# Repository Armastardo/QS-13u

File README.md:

# QS-13u

Un teclado 40% de 13u, diseñado por Quark.Works, inspirado en el layout del Bacca40.

## Layouts

[KLE Link](http://www.keyboard-layout-editor.com/#/gists/edd9330d8816866bf59f697946c975f9)

## Case

QS-13G (gummy worm)

Pendiente, buscar tamaño de oring adecuado

| Qty | Item						| Notes							|
|----:|-------------------------------------------------|-------------------------------------------------------|
|   2	| Tornillo M2.5 x 4 mm						| https://www.mcmaster.com/91290A099/		|
|   4	| Tornillo M2.5 x 10 mm					| https://www.mcmaster.com/91290A103/		|
|   1	| XYZ Daughterboard			| https://github.com/xyzz/xyztkl-r2/tree/main/dboard	|

La version heatset ademas utiliza:
https://www.aliexpress.com/item/1005003174906572.html

| Qty | Item						|
|----:|-------------------------------------------------|
|   2	| Insert M2.5 x 3 x 3.5						|
|   4	| Insert M2.5 x 5 x 3.5					|

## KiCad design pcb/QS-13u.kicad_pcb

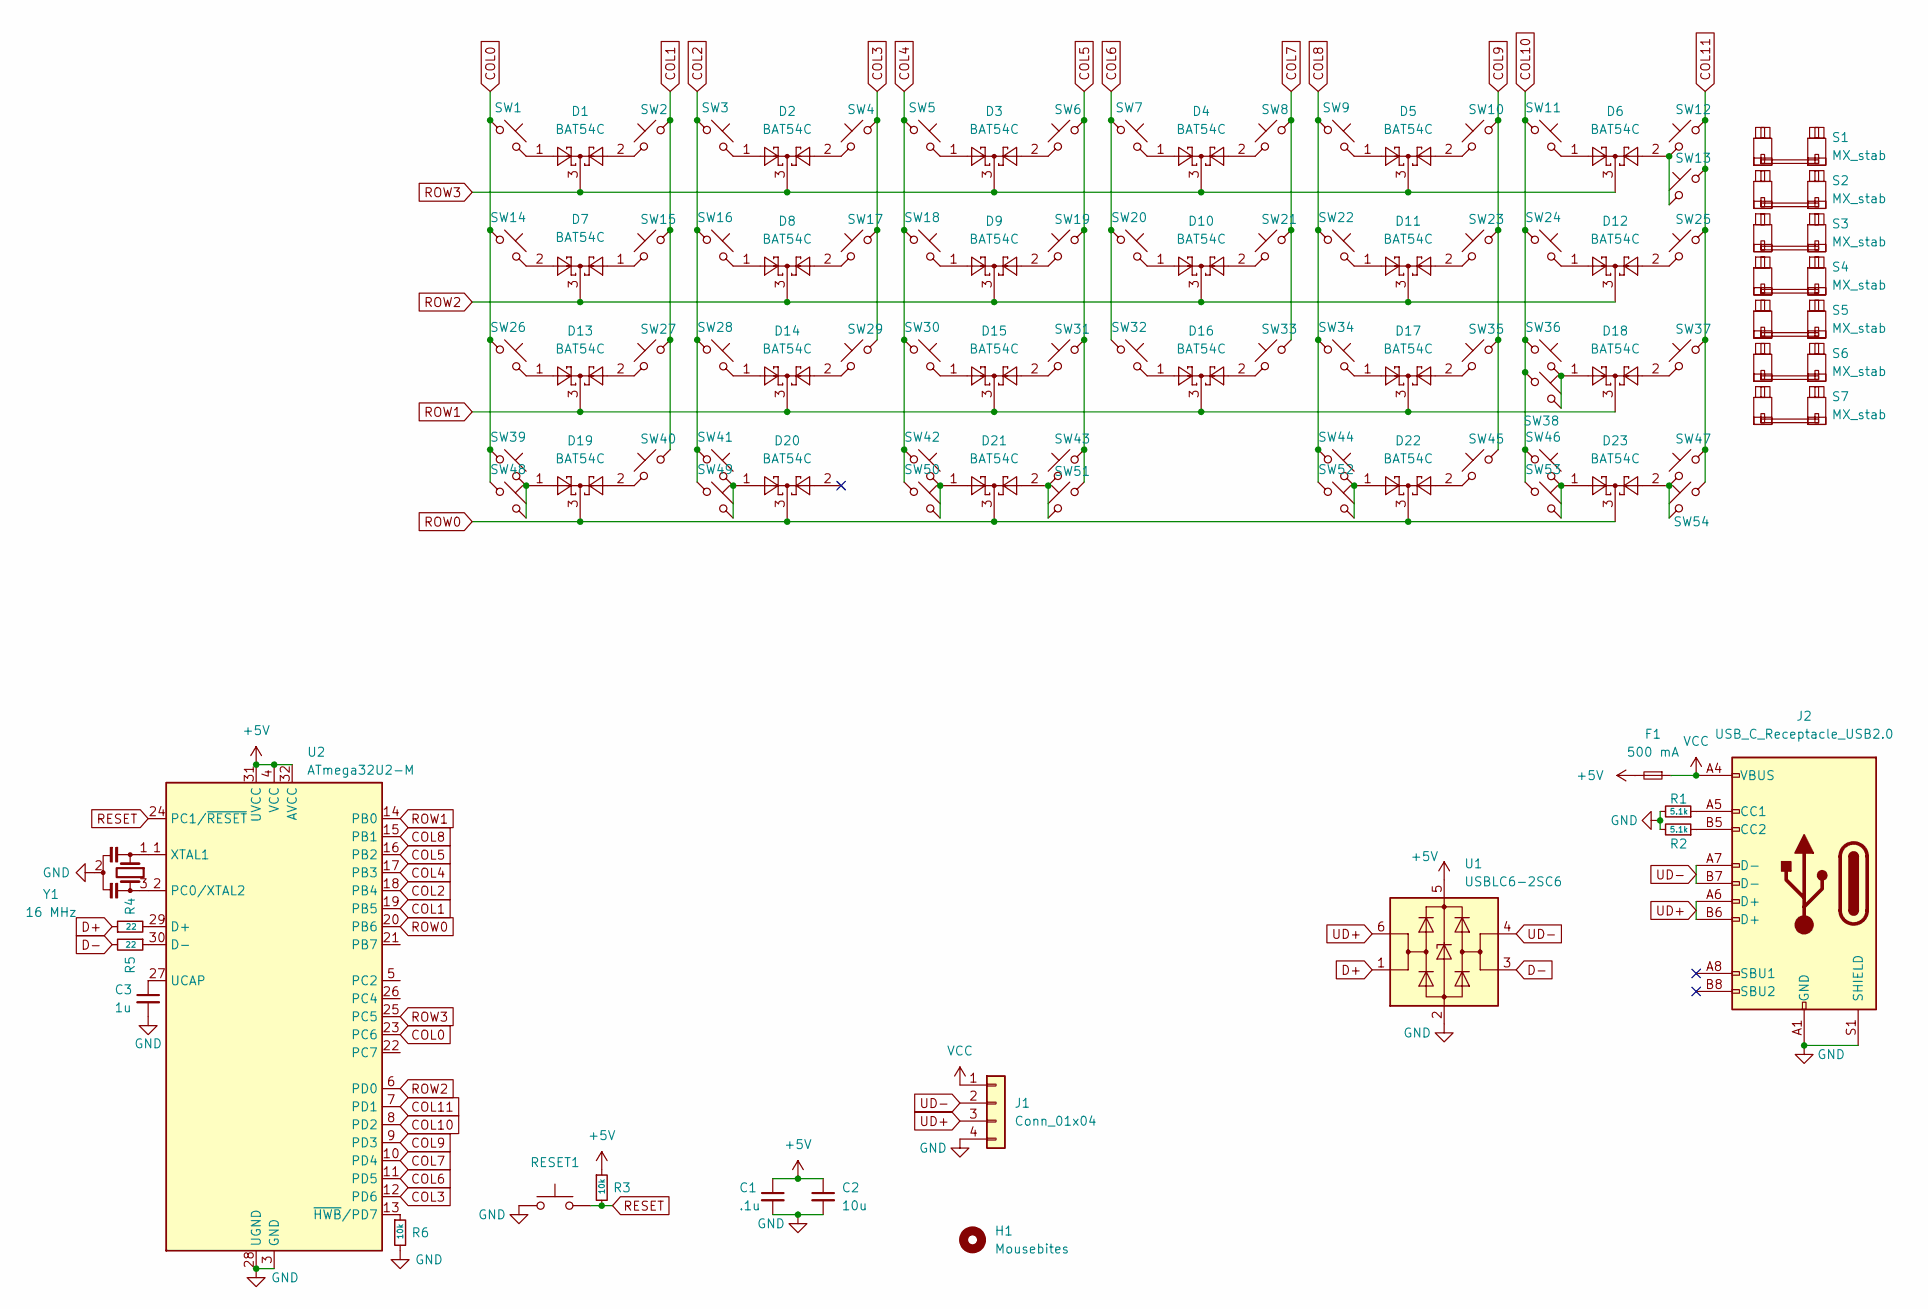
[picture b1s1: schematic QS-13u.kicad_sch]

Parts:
C1: .1u; C_0603_1608Metric
C2: 10u; C_0603_1608Metric
C3: 1u; C_0603_1608Metric
D1, D2, D3, D4, D5, D6, D7, D8, D9, D10, D11, D12, D13, D14, D15, D16, D17, D18, D19, D20, D21, D22, D23: BAT54C; SOT-23
F1: 500 mA; Fuse_1206_3216Metric
H1: Mousebites
J1: Conn_01x04; JST_SH_SM04B-SRSS-TB_1x04-1MP_P1.00mm_Horizontal
J2: USB_C_Receptacle_USB2.0; USB_C_Receptacle_HRO_TYPE-C-31-M-12
R1, R2: 5.1k; R_0603_1608Metric
R3, R6: 10k; R_0603_1608Metric
R4, R5: 22; R_0603_1608Metric
RESET1: SW_Push; SW_SPST_SKQG_WithStem
S1, S2: MX_stab; STAB_MX_3u
S3, S4, S6: MX_stab; STAB_MX_2u
S5: MX_stab; STAB_MX_6u
S7: MX_stab; STAB_MX_7u
SW1, SW2, SW3, SW4, SW5, SW6, SW7, SW8, SW9, SW10, SW11, SW12, SW13, SW15, SW16, SW17, SW18, SW19, SW20, SW21, SW22, SW23, SW24, SW25, SW27, SW28, SW29, SW30, SW31, SW32, SW33, SW34, SW35, SW38, SW40, SW42, SW43, SW45, SW47, SW50, SW51: MX_SW_solder; SW_MX_1u
SW14, SW36, SW39, SW41, SW44, SW46, SW54: MX_SW_solder; SW_MX_1.25u
SW26, SW37: MX_SW_solder; SW_MX_1.75u
SW48, SW49, SW52, SW53: MX_SW_solder; SW_MX_1.5u
U1: USBLC6-2SC6; SOT-23-6
U2: ATmega32U2-M; QFN-32-1EP_5x5mm_P0.5mm_EP3.1x3.1mm
Y1: 16 MHz; Resonator_SMD_Murata_CSTxExxV-3Pin_3.0x1.1mm

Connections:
+5V: C1.1, C2.1, F1.2, R3.1, U1.5 (VBUS), U2.4 (VCC), U2.31 (UVCC), U2.32 (AVCC)
COL0: SW1.1, SW14.1, SW26.1, SW39.1, SW48.1, U2.23 (PC6)
COL1: SW2.2, SW15.2, SW27.2, SW40.2, U2.19 (PB5)
COL2: SW3.1, SW16.1, SW28.1, SW41.1, SW49.1, U2.18 (PB4)
COL3: SW4.2, SW17.2, SW29.2, U2.12 (PD6)
COL4: SW5.1, SW18.1, SW30.1, SW42.1, SW50.1, U2.17 (PB3)
COL5: SW6.2, SW19.2, SW31.2, SW43.2, SW51.2, U2.16 (PB2)
COL6: SW7.1, SW20.1, SW32.1, U2.11 (PD5)
COL7: SW8.2, SW21.2, SW33.2, U2.10 (PD4)
COL8: SW9.1, SW22.1, SW34.1, SW44.1, SW52.1, U2.15 (PB1)
COL9: SW10.2, SW23.2, SW35.2, SW45.2, U2.9 (PD3)
COL10: SW11.1, SW24.1, SW36.1, SW38.1, SW46.1, SW53.1, U2.8 (PD2)
COL11: SW12.2, SW13.2, SW25.2, SW37.2, SW47.2, SW54.2, U2.7 (PD1)
D+: R4.1, U1.1 (I/O1)
D-: R5.2, U1.3 (I/O2)
GND: C1.2, C2.2, C3.2, J1.4, J2.A1 (GND), J2.A12 (GND), J2.B1 (GND), J2.B12 (GND), J2.S1 (SHIELD), R1.2, R2.2, R6.2, RESET1.1, U1.2 (GND), U2.3 (GND), U2.28 (UGND), U2.33 (GND), Y1.2
unnamed: C3.1, U2.27 (UCAP)
unnamed: D1.1, SW1.2
unnamed: D1.2, SW2.1
unnamed: D2.1, SW3.2
unnamed: D2.2, SW4.1
unnamed: D3.1, SW5.2
unnamed: D3.2, SW6.1
unnamed: D4.1, SW7.2
unnamed: D4.2, SW8.1
unnamed: D5.1, SW9.2
unnamed: D5.2, SW10.1
unnamed: D6.1, SW11.2
unnamed: D6.2, SW12.1, SW13.1
unnamed: D7.1, SW15.1
unnamed: D7.2, SW14.2
unnamed: D8.1, SW16.2
unnamed: D8.2, SW17.1
unnamed: D9.1, SW18.2
unnamed: D9.2, SW19.1
unnamed: D10.1, SW20.2
unnamed: D10.2, SW21.1
unnamed: D11.1, SW22.2
unnamed: D11.2, SW23.1
unnamed: D12.1, SW24.2
unnamed: D12.2, SW25.1
unnamed: D13.1, SW26.2
unnamed: D13.2, SW27.1
unnamed: D14.1, SW28.2
unnamed: D14.2, SW29.1
unnamed: D15.1, SW30.2
unnamed: D15.2, SW31.1
unnamed: D16.1, SW32.2
unnamed: D16.2, SW33.1
unnamed: D17.1, SW34.2
unnamed: D17.2, SW35.1
unnamed: D18.1, SW36.2, SW38.2
unnamed: D18.2, SW37.1
unnamed: D19.1, SW39.2, SW48.2
unnamed: D19.2, SW40.1
unnamed: D20.1, SW41.2, SW49.2
unnamed: D21.1, SW42.2, SW50.2
unnamed: D21.2, SW43.1, SW51.1
unnamed: D22.1, SW44.2, SW52.2
unnamed: D22.2, SW45.1
unnamed: D23.1, SW46.2, SW53.2
unnamed: D23.2, SW47.1, SW54.1
unnamed: J2.A5 (CC1), R1.1
unnamed: J2.B5 (CC2), R2.1
unnamed: R4.2, U2.29 (D+)
unnamed: R5.1, U2.30 (D-)
unnamed: R6.1, U2.13 (~HWB/PD7)
unnamed: U2.1 (XTAL1), Y1.1
unnamed: U2.2 (PC0/XTAL2), Y1.3
RESET: R3.2, RESET1.2, U2.24 (PC1/~RESET)
ROW0: D19.3, D20.3, D21.3, D22.3, D23.3, U2.20 (PB6)
ROW1: D13.3, D14.3, D15.3, D16.3, D17.3, D18.3, U2.14 (PB0)
ROW2: D7.3, D8.3, D9.3, D10.3, D11.3, D12.3, U2.6 (PD0)
ROW3: D1.3, D2.3, D3.3, D4.3, D5.3, D6.3, U2.25 (PC5)
UD+: J1.3, J2.A6 (D+), J2.B6 (D+), U1.6 (I/O1)
UD-: J1.2, J2.A7 (D-), J2.B7 (D-), U1.4 (I/O2)
VCC: F1.1, J1.1, J2.A4 (VBUS), J2.A9 (VBUS), J2.B4 (VBUS), J2.B9 (VBUS)

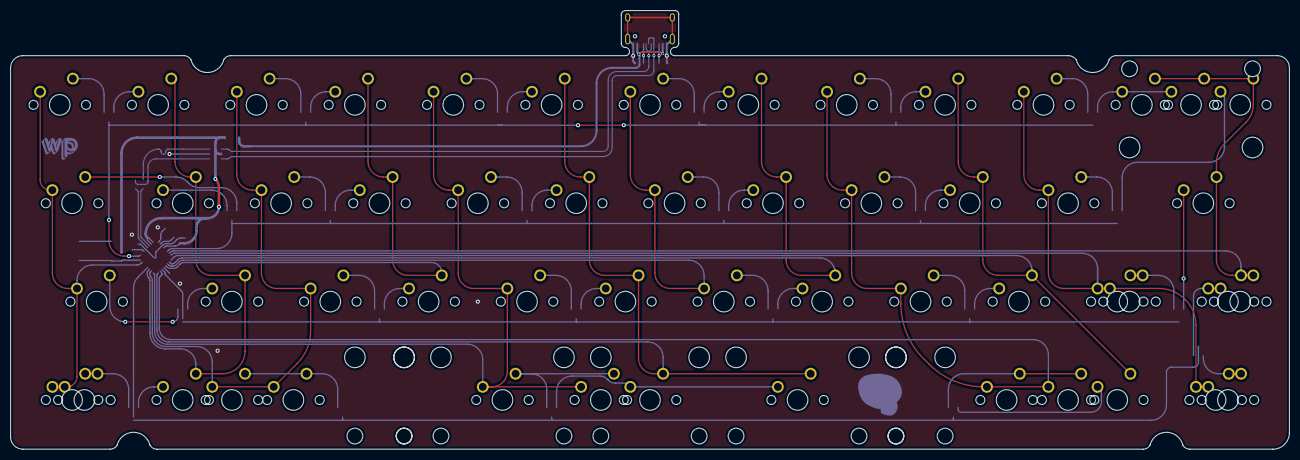
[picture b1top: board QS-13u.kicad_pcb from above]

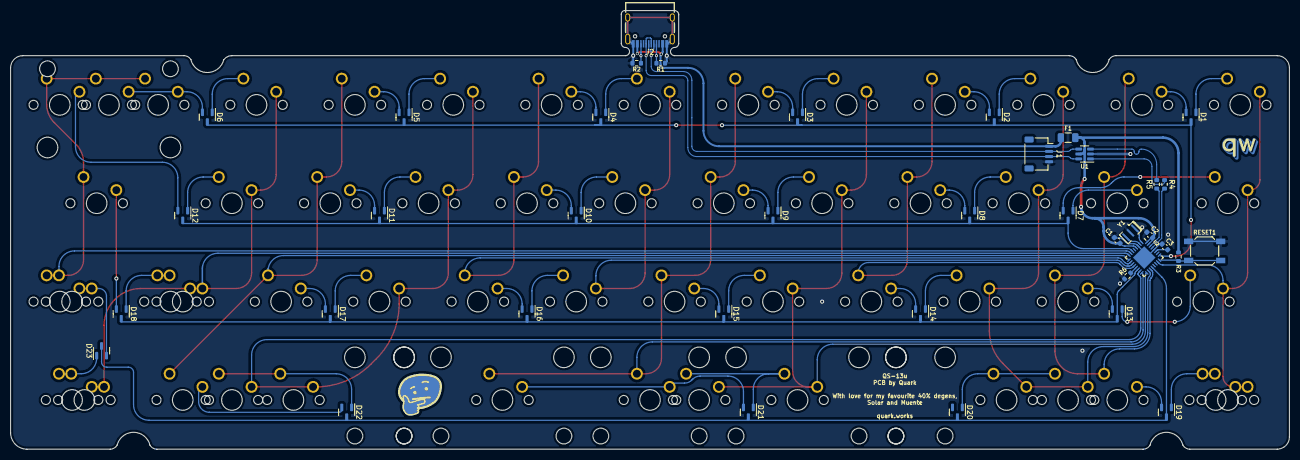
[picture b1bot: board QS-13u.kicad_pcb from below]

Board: 2 copper layers, 247.6 x 84.9 mm, 102 parts (41 on the bottom side), 77 nets.

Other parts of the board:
Ref**: Val**; thinking
Ref**#2: Val**; qw-logo-small

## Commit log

2022-04-27 Initial commit. TODO routing
2022-04-27 gummy worm case, plate
2022-04-28 Undocumented progress
2022-04-28 Moved PCB to pcb folder
2022-04-28 .... actually moved. IDK what tf happened
2022-04-28 Fixes + Updates
    - Fixed some weird submodules shenanigans
    - Repositioned the JST connector
    - Adjusted the outline for gummy o-ring mount
2022-04-28 USB Port + DB Routed
2022-04-28 extra step models
2022-04-28 output pcb 3d models
2022-04-28 eye candy by zetina
2022-04-28 updated case files
2022-04-28 fixed jst channel
2022-04-28 Redesign with xyz db, heatset 3d print version and m2.5 screws
2022-04-28 Fixing readme.md
2022-04-29 top mount version
2022-05-04 PCB Rev.1
    Everything seems to be connected and no obvious errors were found
2022-05-04 Added art and adjusted gerbers
2022-05-04 Afmuente -> Muente
2022-05-17 vial firmware
2022-06-01 fixed rows pinout and unlock keys
2022-06-30 Added thinking svg and kicad footprint
